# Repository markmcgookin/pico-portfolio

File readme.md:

# The Pico Portfolio

This project is an attempt to create a maker-friendly keyboard using the same form factor as the original Atari Portfolio keyboard. 

What started out as an attempt to re-use broken atari portfolio keyboards in new/modern projects hit a wall when tryign to remove the keyboard from its original housing. The housing on the actual Atari Portfolio is very custom for the device and case, and doesn't lend itself well to re-modeling, due to the makeup of the matrix, individual keys and rubber membrane. 

There are files here (in original-portfolio-files) that can be used to turn a *real* atari portfolio keyboard into a USB device with a Raspberry Pi Pico, however, the aim of this repo is to simply create a new, custom board that requires no legacy hardware, is maker friendly, and can be customised with only a 3D printer and some circuitpython.

## Why the portfolio?

Because of its form factor, it is somewhere between the very popular 'blackberry' style handheld keyboard, and the smallest ortholiniar keyboards used in maker projects like cyberdecks. This gives a full keyboard with modifier keys, sacrificing 'touch typing' ability for ease of use by someone who is not an expert in multi-layer keyboard setups. 

Also, John Connor hacked an ATM with one in T2 and I have been in love with them ever since. 

## Why the pico? 

Basically, I had a few picow's lying around and I know the device well. It has lots of GPIO pins and pads under the USB port that make it very easy to solder wires to use as a neat form factor for this sort of thing. 

## Why circuitpython

I plan to add a QMK version to this in the future, and I don't think it would be too hard, but when writing my original version of the firmware for the *real* Portfolio keyboard I ended up using CircuitPython because I knew/understood it well, and was able to make progress. My initial attempts at QMK for that build failed, so I've just stuck with it as it makes debugging super easy. I personally prefer it to MicroPython, but if anyone wants to translate it, please be my guest.

However, now that I know the exact matrix setup, I think QMK would be pretty easy to add to this as an option as well. 

# Setup
You will need to flash a Pico with CircuitPython 9.X (at the time of writing I am using 9.2.7 for the PicoW) - once that is done, connect it to your computer and drop all the files/folders in the `device` folder onto the device. That should load up everything required.

Then it is a matter of printing the STLs in the `3d-models -> stls -> buttons` folder or creating your own. I have included backups of my Fusion360 project in `3d-models -> fusion` should anyone wish to modify things and export their own. I will also include models for the circuitboard with switches and pico in place hopefully will help people wanting to make their own.

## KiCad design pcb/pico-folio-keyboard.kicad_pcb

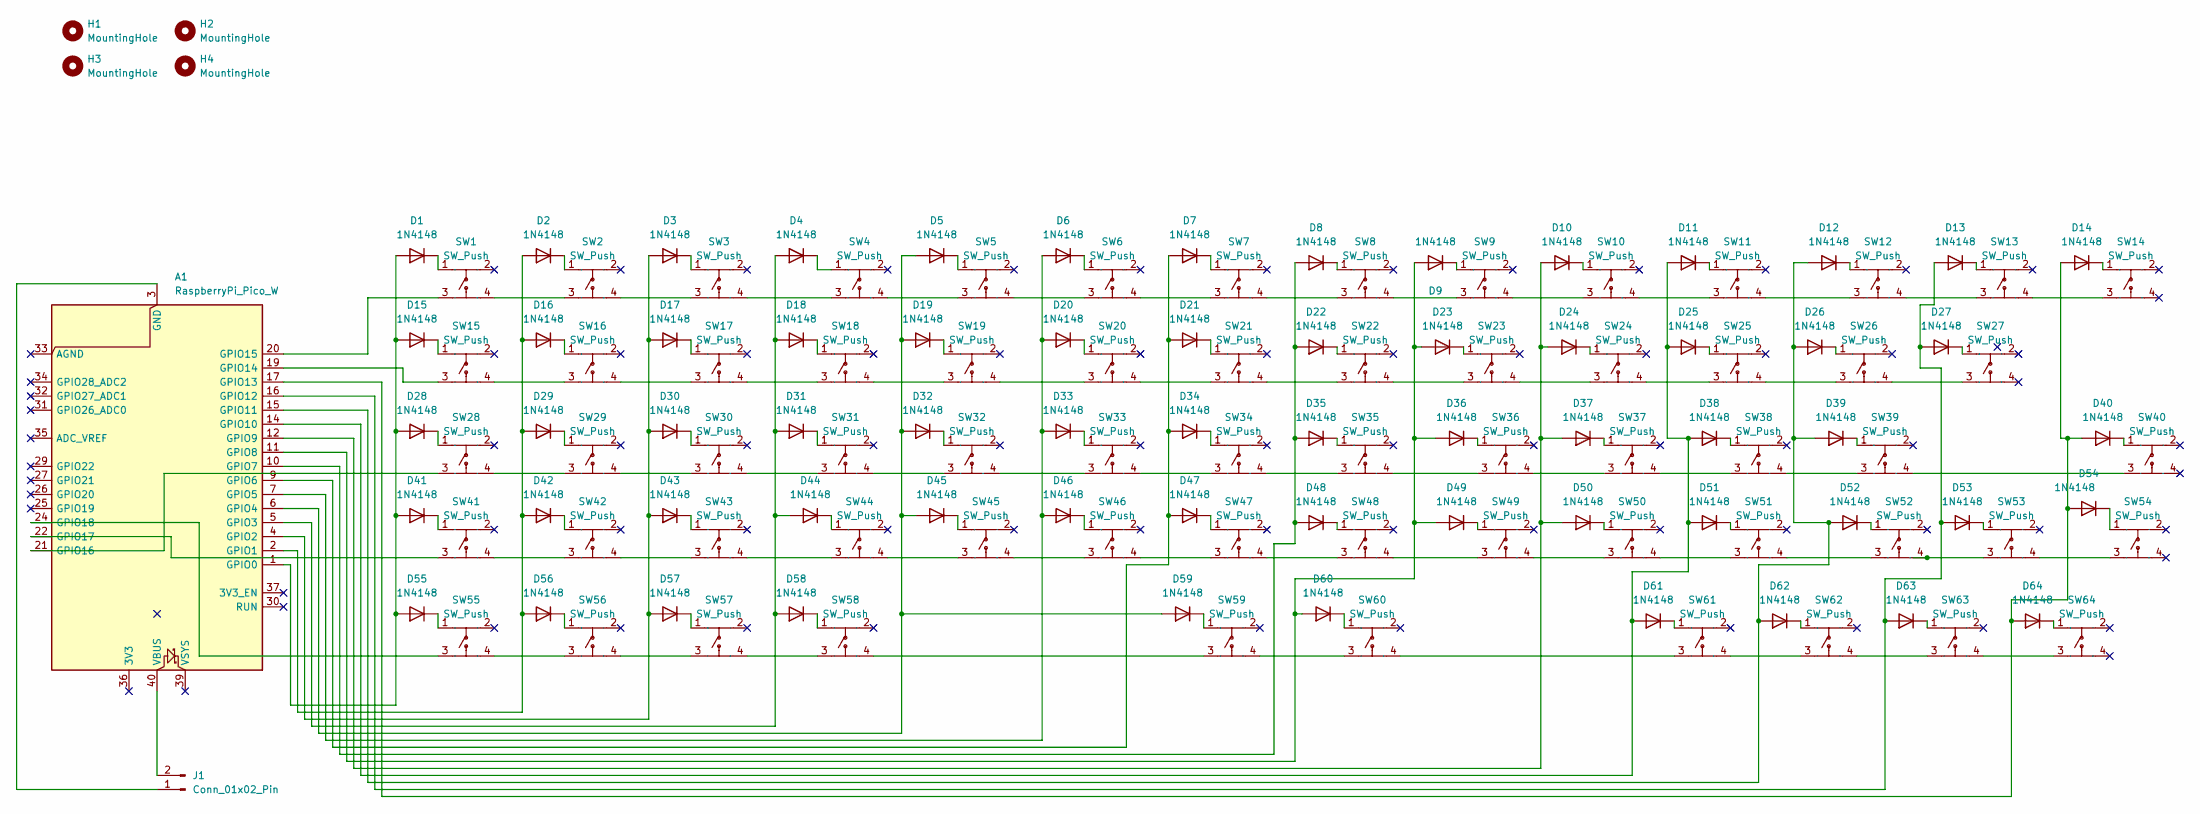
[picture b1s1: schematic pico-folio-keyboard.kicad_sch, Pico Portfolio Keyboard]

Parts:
A1: RaspberryPi_Pico_W; RaspberryPi_Pico_W_SMD_HandSolder
D1, D2, D3, D4, D5, D6, D7, D8, D9, D10, D11, D12, D13, D14, D15, D16, D17, D18, D19, D20, D21, D22, D23, D24, D25, D26, D27, D28, D29, D30, D31, D32, D33, D34, D35, D36, D37, D38, D39, D40, D41, D42, D43, D44, D45, D46, D47, D48, D49, D50, D51, D52, D53, D54, D55, D56, D57, D58, D59, D60, D61, D62, D63, D64: 1N4148; D_DO-35_SOD27_P7.62mm_Horizontal
H1, H2, H3, H4: MountingHole; MountingHole_2.7mm
J1: Conn_01x02_Pin; PinHeader_1x02_P2.54mm_Vertical
SW1, SW2, SW3, SW4, SW5, SW6, SW7, SW8, SW9, SW10, SW11, SW12, SW13, SW14, SW15, SW16, SW17, SW18, SW19, SW20, SW21, SW22, SW23, SW24, SW25, SW26, SW27, SW28, SW29, SW30, SW31, SW32, SW33, SW34, SW35, SW36, SW37, SW38, SW39, SW40, SW41, SW42, SW43, SW44, SW45, SW46, SW47, SW48, SW49, SW50, SW51, SW52, SW53, SW54, SW55, SW56, SW57, SW58, SW59, SW60, SW61, SW62, SW63, SW64: SW_Push; SW-SMD_4P-L6.2-W6.2-P4.50-LS8.6; Manufacturer Part K2-1157SP-I4SW-01; LCSC Part Name 6.4x6.2x3.7红柄开关

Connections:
unnamed: A1.1 (GPIO0), D1.2 (A), D15.2 (A), D28.2 (A), D41.2 (A), D55.2 (A)
unnamed: A1.2 (GPIO1), D2.2 (A), D16.2 (A), D29.2 (A), D42.2 (A), D56.2 (A)
unnamed: A1.4 (GPIO2), D3.2 (A), D17.2 (A), D30.2 (A), D43.2 (A), D57.2 (A)
unnamed: A1.5 (GPIO3), D4.2 (A), D18.2 (A), D31.2 (A), D44.2 (A), D58.2 (A)
unnamed: A1.6 (GPIO4), D5.2 (A), D19.2 (A), D32.2 (A), D45.2 (A), D59.2 (A)
unnamed: A1.7 (GPIO5), D6.2 (A), D20.2 (A), D33.2 (A), D46.2 (A)
unnamed: A1.9 (GPIO6), D7.2 (A), D21.2 (A), D34.2 (A), D47.2 (A)
unnamed: A1.10 (GPIO7), D8.2 (A), D22.2 (A), D35.2 (A), D48.2 (A)
unnamed: A1.11 (GPIO8), D9.2 (A), D23.2 (A), D36.2 (A), D49.2 (A), D60.2 (A)
unnamed: A1.12 (GPIO9), D10.2 (A), D24.2 (A), D37.2 (A), D50.2 (A)
unnamed: A1.14 (GPIO10), D11.2 (A), D25.2 (A), D38.2 (A), D51.2 (A), D61.2 (A)
unnamed: A1.15 (GPIO11), D12.2 (A), D26.2 (A), D39.2 (A), D52.2 (A), D62.2 (A)
unnamed: A1.16 (GPIO12), D13.2 (A), D27.2 (A), D53.2 (A), D63.2 (A)
unnamed: A1.17 (GPIO13), D14.2 (A), D40.2 (A), D54.2 (A), D64.2 (A)
unnamed: A1.19 (GPIO14), SW15.3
unnamed: A1.20 (GPIO15), SW1.3
unnamed: A1.21 (GPIO16), SW28.3
unnamed: A1.22 (GPIO17), SW41.3
unnamed: A1.24 (GPIO18), SW55.3
unnamed: A1.40 (VBUS), J1.2
unnamed: D1.1 (K), SW1.1
unnamed: D2.1 (K), SW2.1
unnamed: D3.1 (K), SW3.1
unnamed: D4.1 (K), SW4.1
unnamed: D5.1 (K), SW5.1
unnamed: D6.1 (K), SW6.1
unnamed: D7.1 (K), SW7.1
unnamed: D8.1 (K), SW8.1
unnamed: D9.1 (K), SW9.1
unnamed: D10.1 (K), SW10.1
unnamed: D11.1 (K), SW11.1
unnamed: D12.1 (K), SW12.1
unnamed: D13.1 (K), SW13.1
unnamed: D14.1 (K), SW14.1
unnamed: D15.1 (K), SW15.1
unnamed: D16.1 (K), SW16.1
unnamed: D17.1 (K), SW17.1
unnamed: D18.1 (K), SW18.1
unnamed: D19.1 (K), SW19.1
unnamed: D20.1 (K), SW20.1
unnamed: D21.1 (K), SW21.1
unnamed: D22.1 (K), SW22.1
unnamed: D23.1 (K), SW23.1
unnamed: D24.1 (K), SW24.1
unnamed: D25.1 (K), SW25.1
unnamed: D26.1 (K), SW26.1
unnamed: D27.1 (K), SW27.1
unnamed: D28.1 (K), SW28.1
unnamed: D29.1 (K), SW29.1
unnamed: D30.1 (K), SW30.1
unnamed: D31.1 (K), SW31.1
unnamed: D32.1 (K), SW32.1
unnamed: D33.1 (K), SW33.1
unnamed: D34.1 (K), SW34.1
unnamed: D35.1 (K), SW35.1
unnamed: D36.1 (K), SW36.1
unnamed: D37.1 (K), SW37.1
unnamed: D38.1 (K), SW38.1
unnamed: D39.1 (K), SW39.1
unnamed: D40.1 (K), SW40.1
unnamed: D41.1 (K), SW41.1
unnamed: D42.1 (K), SW42.1
unnamed: D43.1 (K), SW43.1
unnamed: D44.1 (K), SW44.1
unnamed: D45.1 (K), SW45.1
unnamed: D46.1 (K), SW46.1
unnamed: D47.1 (K), SW47.1
unnamed: D48.1 (K), SW48.1
unnamed: D49.1 (K), SW49.1
unnamed: D50.1 (K), SW50.1
unnamed: D51.1 (K), SW51.1
unnamed: D52.1 (K), SW52.1
unnamed: D53.1 (K), SW53.1
unnamed: D54.1 (K), SW54.1
unnamed: D55.1 (K), SW55.1
unnamed: D56.1 (K), SW56.1
unnamed: D57.1 (K), SW57.1
unnamed: D58.1 (K), SW58.1
unnamed: D59.1 (K), SW59.1
unnamed: D60.1 (K), SW60.1
unnamed: D61.1 (K), SW61.1
unnamed: D62.1 (K), SW62.1
unnamed: D63.1 (K), SW63.1
unnamed: D64.1 (K), SW64.1
unnamed: A1.3 (GND), A1.8 (GND), A1.13 (GND), A1.18 (GND), A1.23 (GND), A1.28 (GND), A1.38 (GND), J1.1
unnamed: SW1.4, SW2.3
unnamed: SW2.4, SW3.3
unnamed: SW3.4, SW4.3
unnamed: SW4.4, SW5.3
unnamed: SW5.4, SW6.3
unnamed: SW6.4, SW7.3
unnamed: SW7.4, SW8.3
unnamed: SW8.4, SW9.3
unnamed: SW9.4, SW10.3
unnamed: SW10.4, SW11.3
unnamed: SW11.4, SW12.3
unnamed: SW12.4, SW13.3
unnamed: SW13.4, SW14.3
unnamed: SW15.4, SW16.3
unnamed: SW16.4, SW17.3
unnamed: SW17.4, SW18.3
unnamed: SW18.4, SW19.3
unnamed: SW19.4, SW20.3
unnamed: SW20.4, SW21.3
unnamed: SW21.4, SW22.3
unnamed: SW22.4, SW23.3
unnamed: SW23.4, SW24.3
unnamed: SW24.4, SW25.3
unnamed: SW25.4, SW26.3
unnamed: SW26.4, SW27.3
unnamed: SW28.4, SW29.3
unnamed: SW29.4, SW30.3
unnamed: SW30.4, SW31.3
unnamed: SW31.4, SW32.3
unnamed: SW32.4, SW33.3
unnamed: SW33.4, SW34.3
unnamed: SW34.4, SW35.3
unnamed: SW35.4, SW36.3
unnamed: SW36.4, SW37.3
unnamed: SW37.4, SW38.3
unnamed: SW38.4, SW39.3
unnamed: SW39.4, SW40.3
unnamed: SW41.4, SW42.3
unnamed: SW42.4, SW43.3
unnamed: SW43.4, SW44.3
unnamed: SW44.4, SW45.3
unnamed: SW45.4, SW46.3
unnamed: SW46.4, SW47.3
unnamed: SW47.4, SW48.3
unnamed: SW48.4, SW49.3
unnamed: SW49.4, SW50.3
unnamed: SW50.4, SW51.3
unnamed: SW51.4, SW52.3
unnamed: SW52.4, SW53.3
unnamed: SW53.4, SW54.3
unnamed: SW55.4, SW56.3
unnamed: SW56.4, SW57.3
unnamed: SW57.4, SW58.3
unnamed: SW58.4, SW59.3
unnamed: SW59.4, SW60.3
unnamed: SW60.4, SW61.3
unnamed: SW61.4, SW62.3
unnamed: SW62.4, SW63.3
unnamed: SW63.4, SW64.3

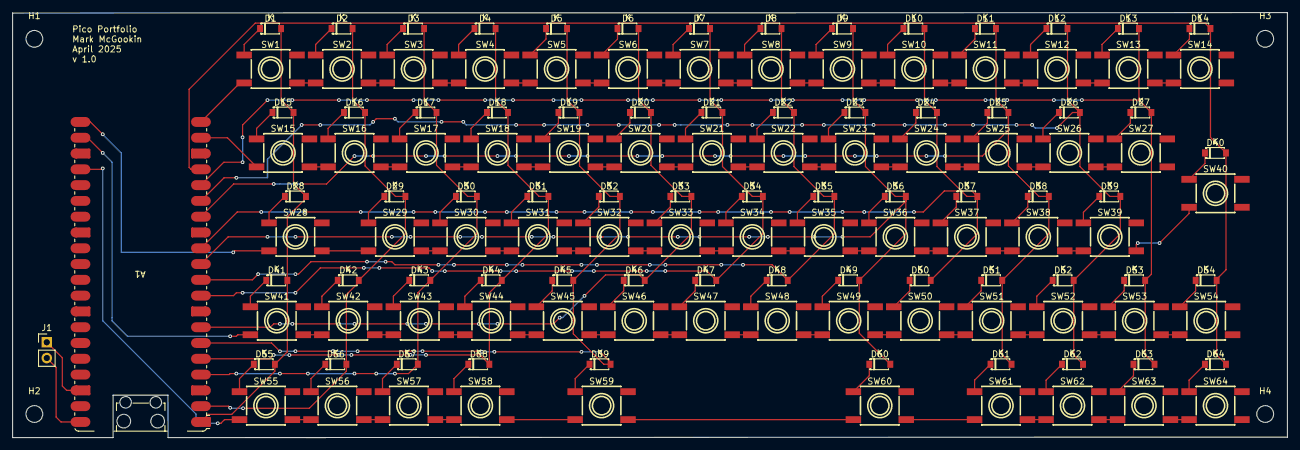
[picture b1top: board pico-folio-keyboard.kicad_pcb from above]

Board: 2 copper layers, 205.1 x 68.4 mm, 134 parts (0 on the bottom side), 144 nets.

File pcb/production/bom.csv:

Designator,Footprint,Quantity,Value,LCSC Part #
"D1, D10, D11, D12, D13, D14, D15, D16, D17, D18, D19, D2, D20, D21, D22, D23, D24, D25, D26, D27, D28, D29, D3, D30, D31, D32, D33, D34, D35, D36, D37, D38, D39, D4, D40, D41, D42, D43, D44, D45, D46, D47, D48, D49, D5, D50, D51, D52, D53, D54, D55, D56, D57, D58, D59, D6, D60, D61, D62, D63, D64, D7, D8, D9",SOD-123_L2.8-W1.8-LS3.7-RD,64,1N4148,
"SW1, SW10, SW11, SW12, SW13, SW14, SW15, SW16, SW17, SW18, SW19, SW2, SW20, SW21, SW22, SW23, SW24, SW25, SW26, SW27, SW28, SW29, SW3, SW30, SW31, SW32, SW33, SW34, SW35, SW36, SW37, SW38, SW39, SW4, SW40, SW41, SW42, SW43, SW44, SW45, SW46, SW47, SW48, SW49, SW5, SW50, SW51, SW52, SW53, SW54, SW55, SW56, SW57, SW58, SW59, SW6, SW60, SW61, SW62, SW63, SW64, SW7, SW8, SW9",SW-SMD_4P-L6.2-W6.2-P4.50-LS8.6,64,SW_Push,

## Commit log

2025-04-07 Added QMK keyboard folder
2025-04-08 backed up log out put and python script before changing to try and create a circuitpython keyboard
2025-04-08 Removed older files and qmk stuff. Got a basic version of this working with circuitpython
2025-04-14 updated with function keys
2025-04-24 pcb design
2025-05-06 checking in everything before a refactor
2025-05-06 Refactored git repo with current state of project.
2025-05-06 added readme
2025-05-09 Updated 3D models and print files
2025-05-10 added stl
2025-05-15 updated schematic and pcb to break out vbus and gnd for usb without bodge wires
2025-05-15 Tweaked settings to remove header from BOM and 3D view
